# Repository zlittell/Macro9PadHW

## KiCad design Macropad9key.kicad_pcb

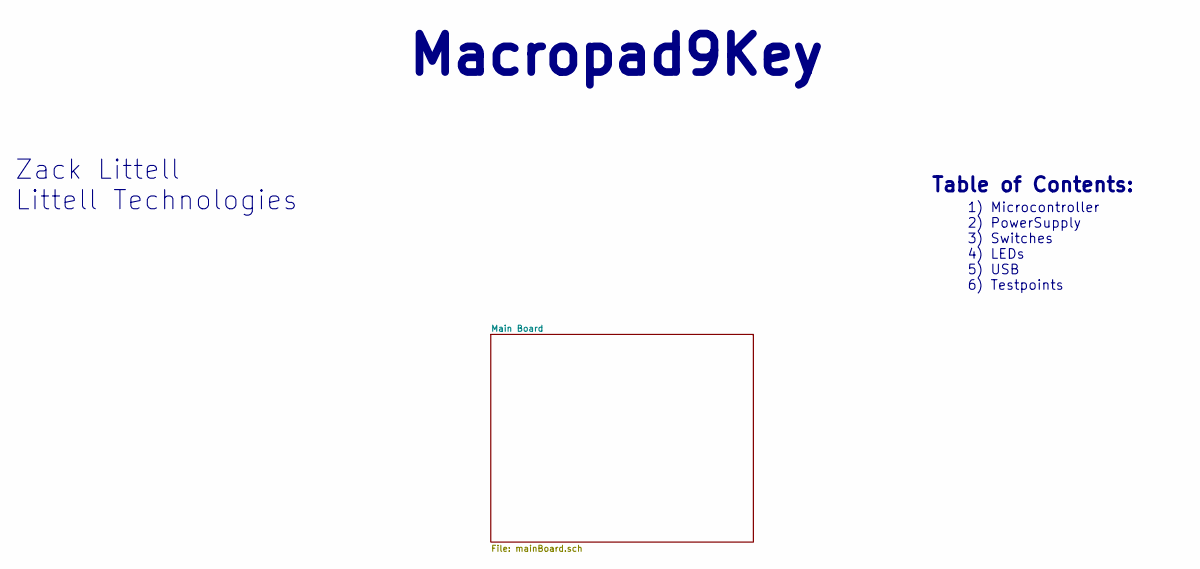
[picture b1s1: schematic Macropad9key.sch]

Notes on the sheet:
Macropad9Key
Zack Littell
Littell Technologies
Table of Contents:
1) Microcontroller 2) PowerSupply 3) Switches 4) LEDs 5) USB 6) Testpoints

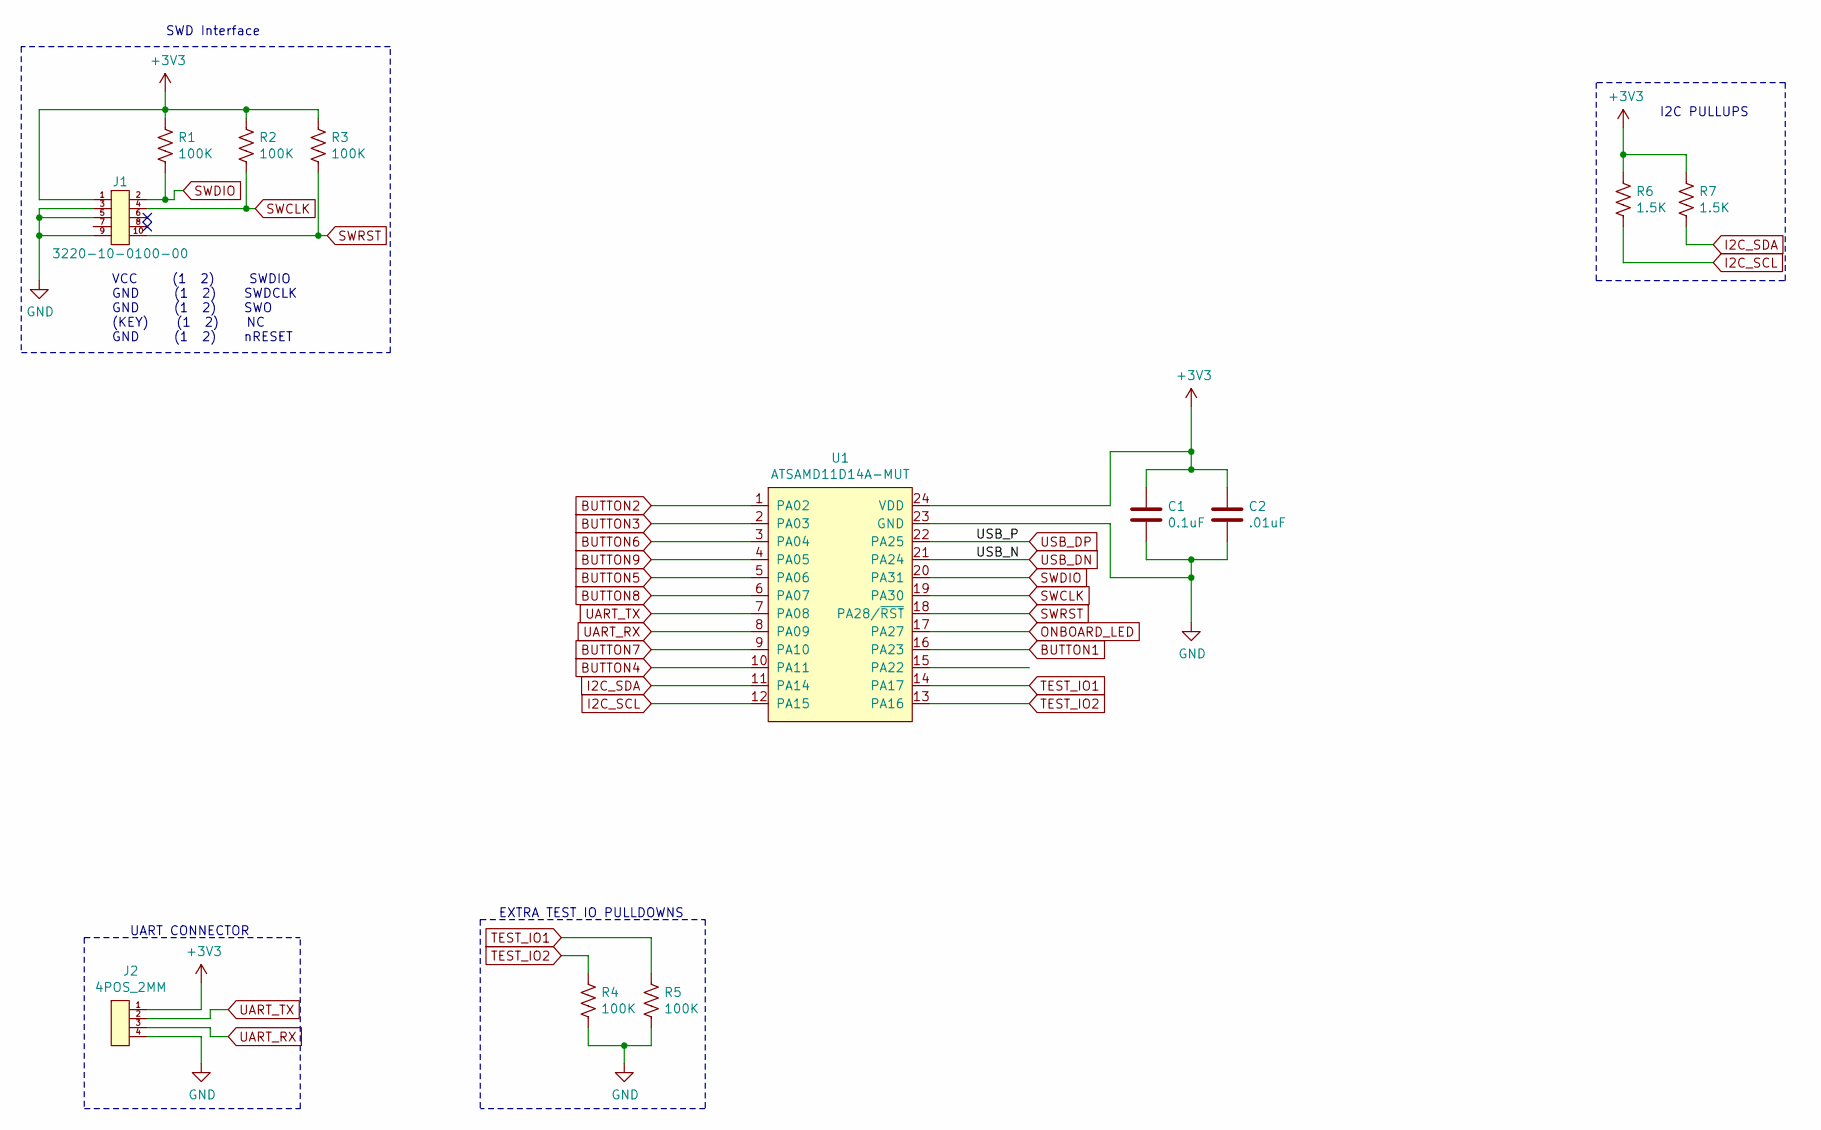
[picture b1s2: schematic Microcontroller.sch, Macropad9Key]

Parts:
C1: 0.1uF; C_0402_1005Metric
C2: .01uF; C_0402_1005Metric
J1: 3220-10-0100-00
J2: 4POS_2MM
R1, R2, R3, R4, R5: 100K; R_0603_1608Metric
R6, R7: 1.5K; R_0603_1608Metric
U1: ATSAMD11D14A-MUT; QFN-24-1EP_4x4mm_P0.5mm_EP2.6x2.6mm

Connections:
+3V3: C1.1, C2.1, J1.1, J2.1, R1.1, R2.1, R3.1, R6.1, R7.1, U1.24 (VDD); also elsewhere on the board
BUTTON1: U1.16 (PA23); also elsewhere on the board
BUTTON2: U1.1 (PA02); also elsewhere on the board
BUTTON3: U1.2 (PA03); also elsewhere on the board
BUTTON4: U1.10 (PA11); also elsewhere on the board
BUTTON5: U1.5 (PA06); also elsewhere on the board
BUTTON6: U1.3 (PA04); also elsewhere on the board
BUTTON7: U1.9 (PA10); also elsewhere on the board
BUTTON8: U1.6 (PA07); also elsewhere on the board
BUTTON9: U1.4 (PA05); also elsewhere on the board
GND: C1.2, C2.2, J1.3, J1.5, J1.9, J2.4, R4.2, R5.2, U1.23 (GND); also elsewhere on the board
I2C_SCL: R6.2, U1.12 (PA15); also elsewhere on the board
I2C_SDA: R7.2, U1.11 (PA14); also elsewhere on the board
ONBOARD_LED: U1.17 (PA27); also elsewhere on the board
SWCLK: J1.4, R2.2, U1.19 (PA30); also elsewhere on the board
SWDIO: J1.2, R1.2, U1.20 (PA31); also elsewhere on the board
SWRST: J1.10, R3.2, U1.18 (PA28/~RST); also elsewhere on the board
TEST_IO1: R5.1, U1.14 (PA17); also elsewhere on the board
TEST_IO2: R4.1, U1.13 (PA16); also elsewhere on the board
UART_RX: J2.3, U1.8 (PA09); also elsewhere on the board
UART_TX: J2.2, U1.7 (PA08); also elsewhere on the board
USB_DN: U1.21 (PA24); also elsewhere on the board
USB_DP: U1.22 (PA25); also elsewhere on the board

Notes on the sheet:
I2C PULLUPS
VCC (1 2) SWDIO GND (1 2) SWDCLK GND (1 2) SWO (KEY) (1 2) NC GND (1 2) nRESET
SWD Interface
UART CONNECTOR
EXTRA TEST IO PULLDOWNS

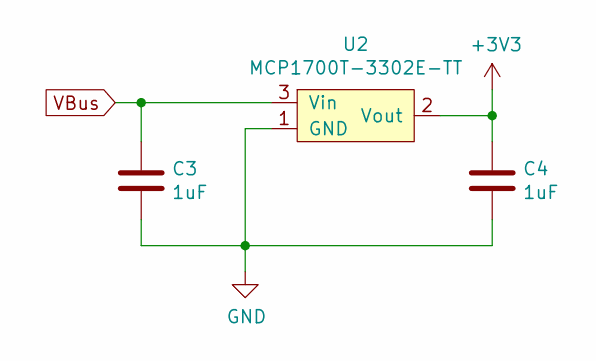
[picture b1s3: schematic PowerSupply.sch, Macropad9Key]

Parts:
C3, C4: 1uF; C_0603_1608Metric
U2: MCP1700T-3302E-TT; SOT-23

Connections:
+3V3: C4.1, U2.2 (Vout); also elsewhere on the board
GND: C3.2, C4.2, U2.1 (GND); also elsewhere on the board
VBus: C3.1, U2.3 (Vin); also elsewhere on the board

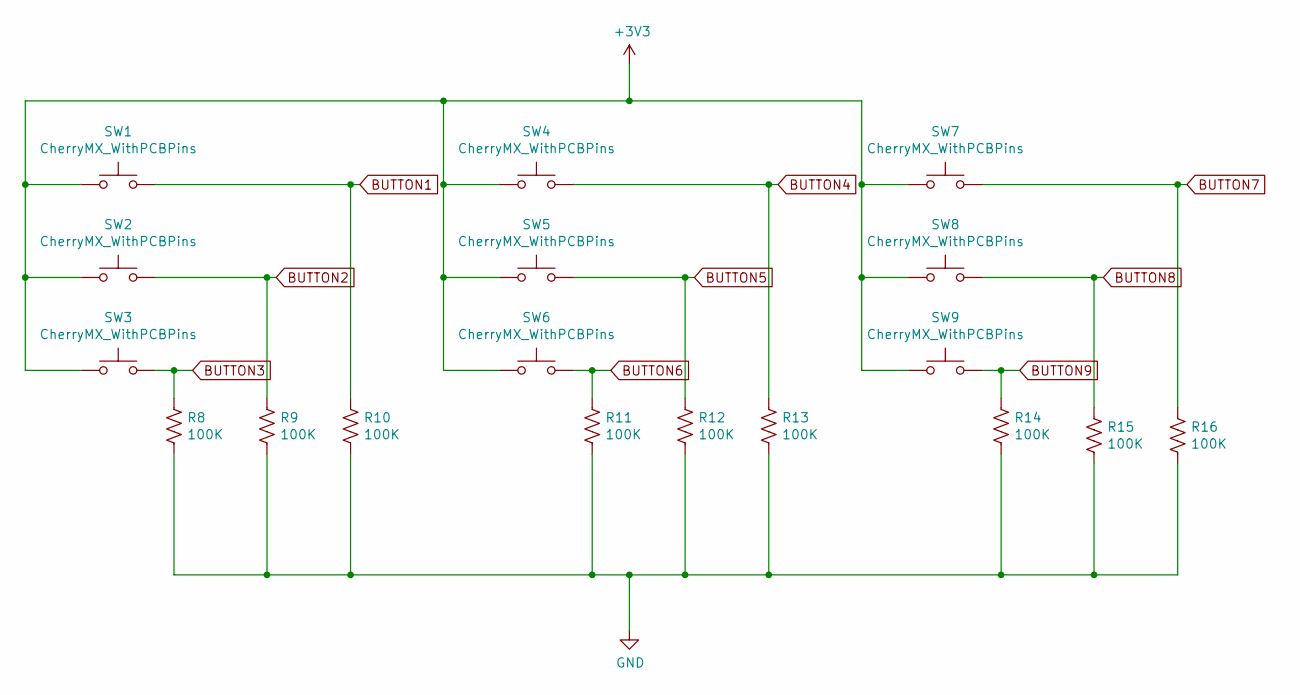
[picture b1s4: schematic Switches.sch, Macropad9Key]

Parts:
R8, R9, R10, R11, R12, R13, R14, R15, R16: 100K; R_0603_1608Metric
SW1, SW2, SW3, SW4, SW5, SW6, SW7, SW8, SW9: CherryMX_WithPCBPins; SW_Cherry_MX_1.00u_PCB

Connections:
+3V3: SW1.1, SW2.1, SW3.1, SW4.1, SW5.1, SW6.1, SW7.1, SW8.1, SW9.1; also elsewhere on the board
BUTTON1: R10.1, SW1.2; also elsewhere on the board
BUTTON2: R9.1, SW2.2; also elsewhere on the board
BUTTON3: R8.1, SW3.2; also elsewhere on the board
BUTTON4: R13.1, SW4.2; also elsewhere on the board
BUTTON5: R12.1, SW5.2; also elsewhere on the board
BUTTON6: R11.1, SW6.2; also elsewhere on the board
BUTTON7: R16.1, SW7.2; also elsewhere on the board
BUTTON8: R15.1, SW8.2; also elsewhere on the board
BUTTON9: R14.1, SW9.2; also elsewhere on the board
GND: R8.2, R9.2, R10.2, R11.2, R12.2, R13.2, R14.2, R15.2, R16.2; also elsewhere on the board

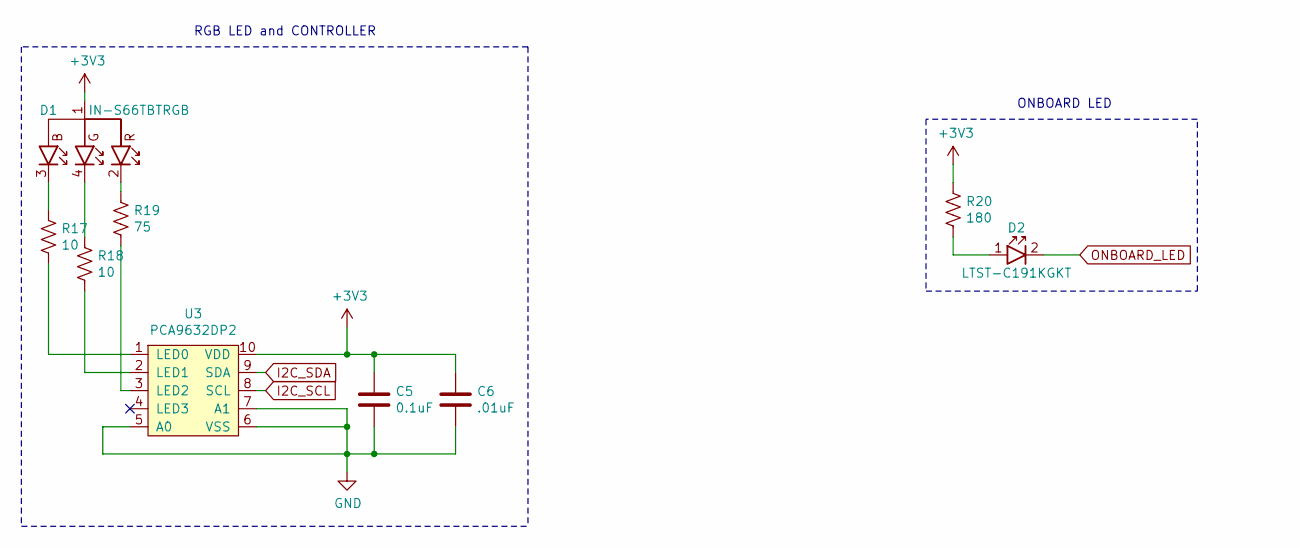
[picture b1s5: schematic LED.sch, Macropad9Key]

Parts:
C5: 0.1uF; C_0402_1005Metric
C6: .01uF; C_0402_1005Metric
D1: IN-S66TBTRGB; 0606_1616Metric
D2: LTST-C191KGKT; LED_0603_1608Metric
R17, R18: 10; R_0603_1608Metric
R19: 75; R_0603_1608Metric
R20: 180; R_0603_1608Metric
U3: PCA9632DP2; TSSOP-10_3x3mm_P0.5mm

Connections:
+3V3: C5.1, C6.1, D1.1 (CA), R20.1, U3.10 (VDD); also elsewhere on the board
GND: C5.2, C6.2, U3.5 (A0), U3.6 (VSS), U3.7 (A1); also elsewhere on the board
I2C_SCL: U3.8 (SCL); also elsewhere on the board
I2C_SDA: U3.9 (SDA); also elsewhere on the board
unnamed: D1.2 (R), R19.1
unnamed: D1.3 (B), R17.2
unnamed: D1.4 (G), R18.2
unnamed: D2.1 (ANNODE), R20.2
unnamed: R17.1, U3.1 (LED0)
unnamed: R18.1, U3.2 (LED1)
unnamed: R19.2, U3.3 (LED2)
ONBOARD_LED: D2.2 (Cathode); also elsewhere on the board

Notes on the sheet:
ONBOARD LED
RGB LED and CONTROLLER

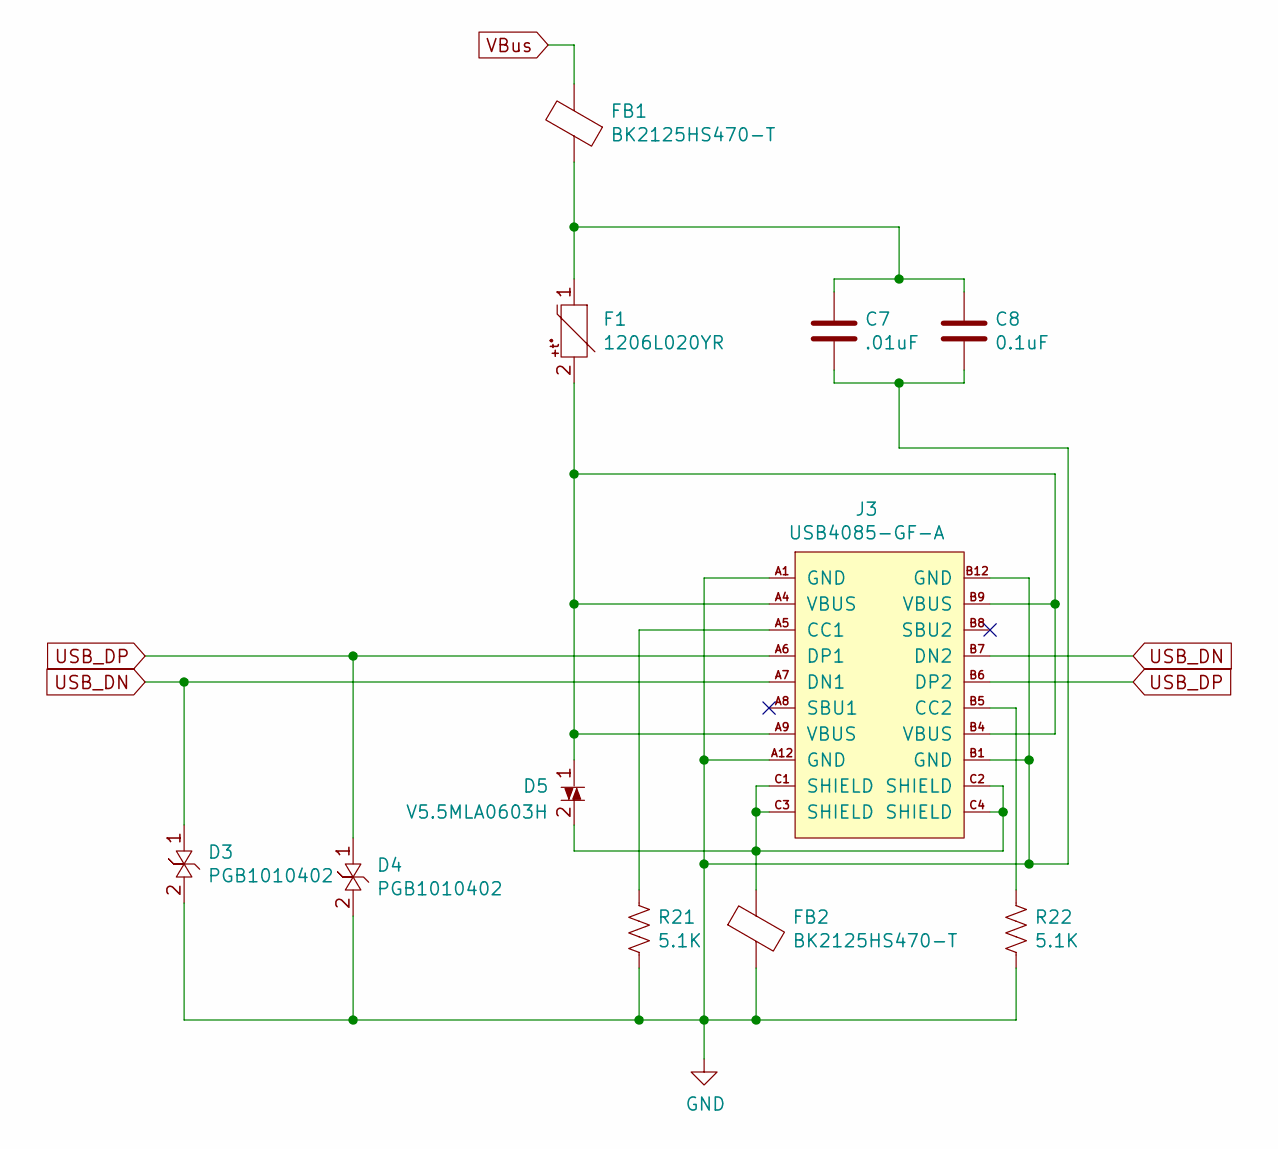
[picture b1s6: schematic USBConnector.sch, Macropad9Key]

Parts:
C7: .01uF; C_0402_1005Metric
C8: 0.1uF; C_0402_1005Metric
D3, D4: PGB1010402; D_0402_1005Metric_NP
D5: V5.5MLA0603H; D_0603_1608Metric_NP
F1: 1206L020YR; Fuse_1206_3216Metric
FB1, FB2: BK2125HS470-T; L_0805_2012Metric
J3: USB4085-GF-A
R21, R22: 5.1K; R_0603_1608Metric

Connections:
GND: C7.2, C8.2, D3.2, D4.2, FB2.2, J3.A1 (GND), J3.A12 (GND), J3.B1 (GND), J3.B12 (GND), R21.2, R22.2; also elsewhere on the board
unnamed: C7.1, C8.1, F1.1, FB1.1
unnamed: D5.1, F1.2, J3.A4 (VBUS), J3.A9 (VBUS), J3.B4 (VBUS), J3.B9 (VBUS)
unnamed: D5.2, FB2.1, J3.C1 (SHIELD), J3.C2 (SHIELD), J3.C3 (SHIELD), J3.C4 (SHIELD)
unnamed: J3.A5 (CC1), R21.1
unnamed: J3.B5 (CC2), R22.1
USB_DN: D3.1, J3.A7 (DN1), J3.B7 (DN2); also elsewhere on the board
USB_DP: D4.1, J3.A6 (DP1), J3.B6 (DP2); also elsewhere on the board
VBus: FB1.2; also elsewhere on the board

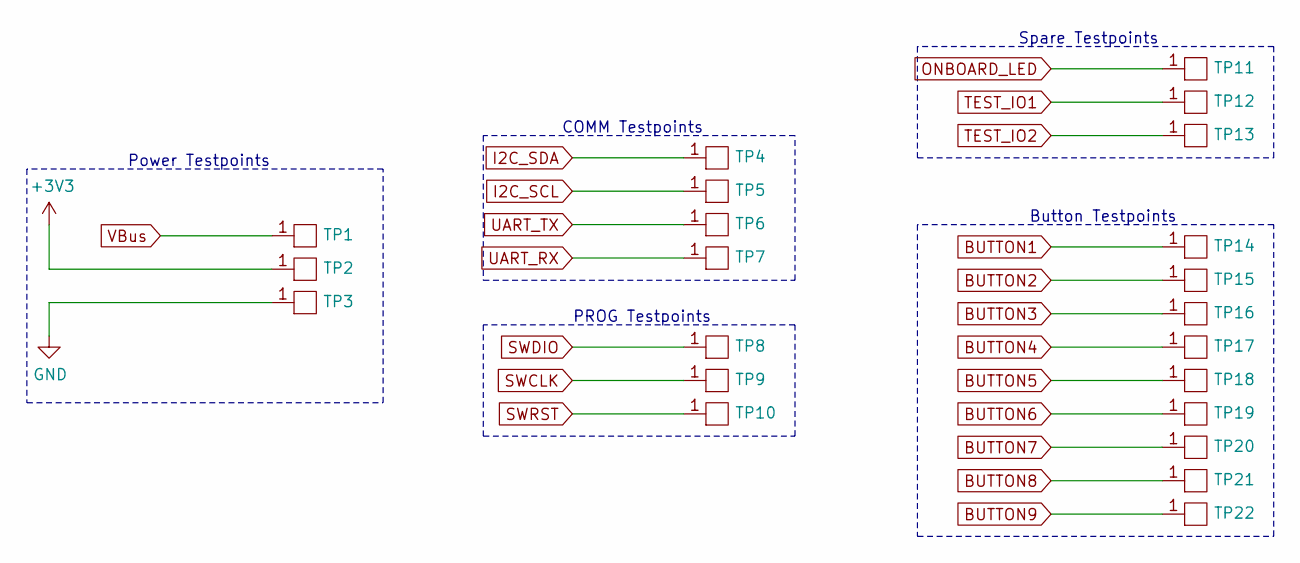
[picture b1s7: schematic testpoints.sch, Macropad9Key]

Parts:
TP1, TP2, TP3, TP4, TP5, TP6, TP7, TP8, TP9, TP10, TP11, TP12, TP13, TP14, TP15, TP16, TP17, TP18, TP19, TP20, TP21, TP22: TESTPOINT_50MILSQ

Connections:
+3V3: TP2.1; also elsewhere on the board
BUTTON1: TP14.1; also elsewhere on the board
BUTTON2: TP15.1; also elsewhere on the board
BUTTON3: TP16.1; also elsewhere on the board
BUTTON4: TP17.1; also elsewhere on the board
BUTTON5: TP18.1; also elsewhere on the board
BUTTON6: TP19.1; also elsewhere on the board
BUTTON7: TP20.1; also elsewhere on the board
BUTTON8: TP21.1; also elsewhere on the board
BUTTON9: TP22.1; also elsewhere on the board
GND: TP3.1; also elsewhere on the board
I2C_SCL: TP5.1; also elsewhere on the board
I2C_SDA: TP4.1; also elsewhere on the board
ONBOARD_LED: TP11.1; also elsewhere on the board
SWCLK: TP9.1; also elsewhere on the board
SWDIO: TP8.1; also elsewhere on the board
SWRST: TP10.1; also elsewhere on the board
TEST_IO1: TP12.1; also elsewhere on the board
TEST_IO2: TP13.1; also elsewhere on the board
UART_RX: TP7.1; also elsewhere on the board
UART_TX: TP6.1; also elsewhere on the board
VBus: TP1.1; also elsewhere on the board

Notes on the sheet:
Power Testpoints
COMM Testpoints
Spare Testpoints
PROG Testpoints
Button Testpoints

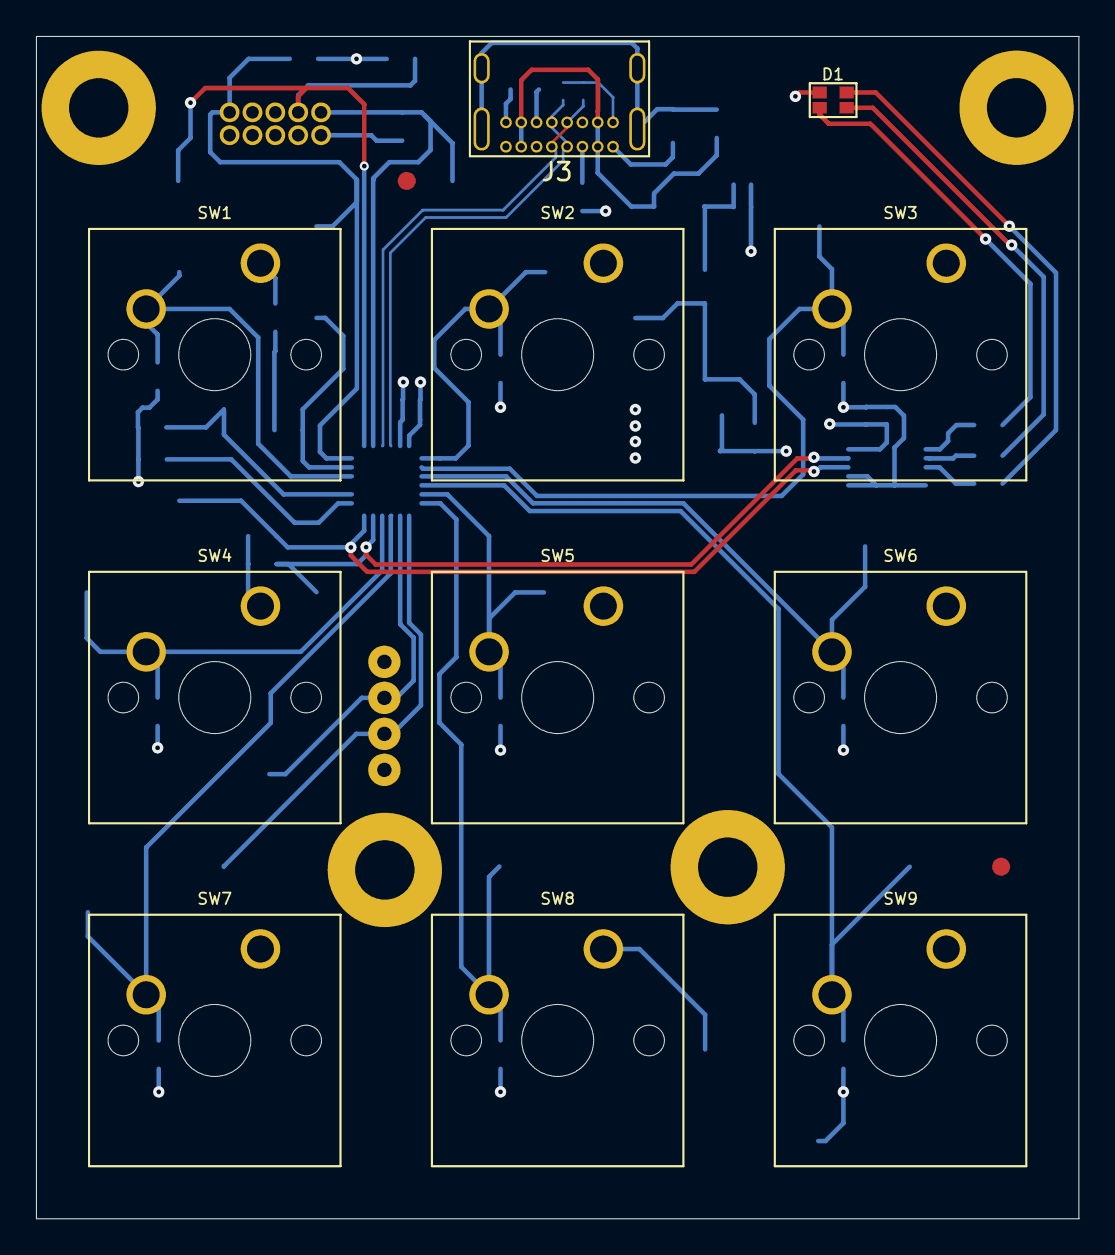
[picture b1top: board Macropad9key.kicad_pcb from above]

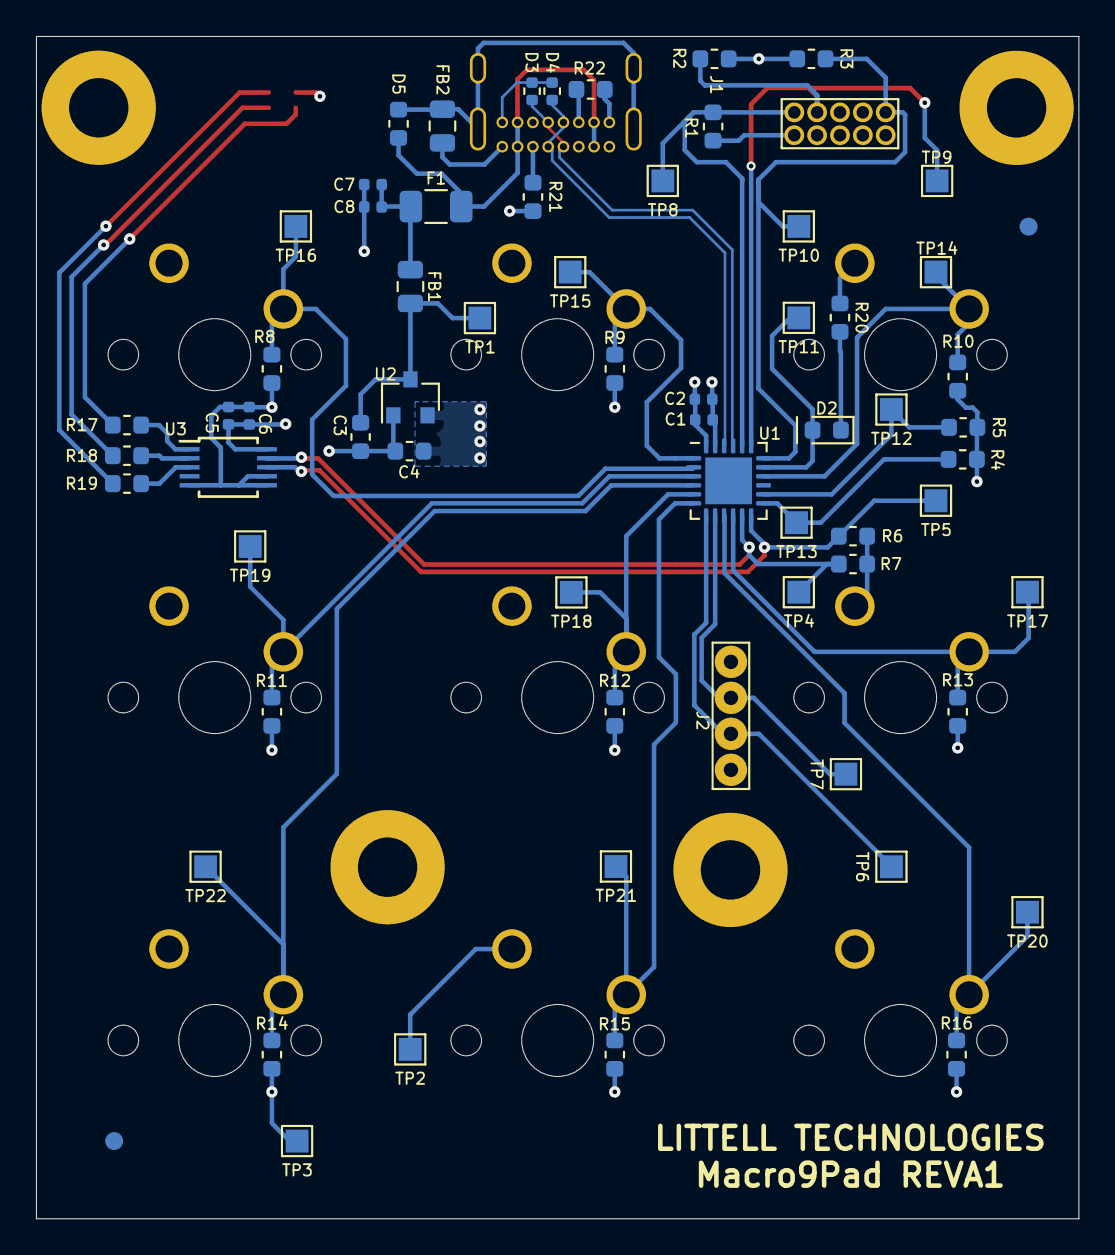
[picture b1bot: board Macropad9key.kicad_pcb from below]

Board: 4 copper layers, 57.9 x 65.7 mm, 75 parts (64 on the bottom side), 36 nets.

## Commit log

2020-08-29 Schematic Done Starting PCB Initial Commit
2020-08-29 Placed components, USB difference calc'd
2020-08-30 Initial layout complete. Pins moved to make layout easy
2020-08-31 Silkscreen REFDES resized and aligned
2020-08-31 Adjust assembly layer. Add Fiducial Marks on SMD side
2020-09-01 Create pcb export step file for MCAD.
2020-09-01 Shrink PCB, move LED to opposite corner top side
2020-09-02 Fix mounting screw hole under ICD header
2020-09-02 updated pcb 3d step file export
2020-09-02 Update titleblock, add fab notes, add drill table
2020-09-02 Gerbers for REVA1 created
2020-09-02 Add company and pcb name/rev to silk
2020-09-02 fix outputs having title block
